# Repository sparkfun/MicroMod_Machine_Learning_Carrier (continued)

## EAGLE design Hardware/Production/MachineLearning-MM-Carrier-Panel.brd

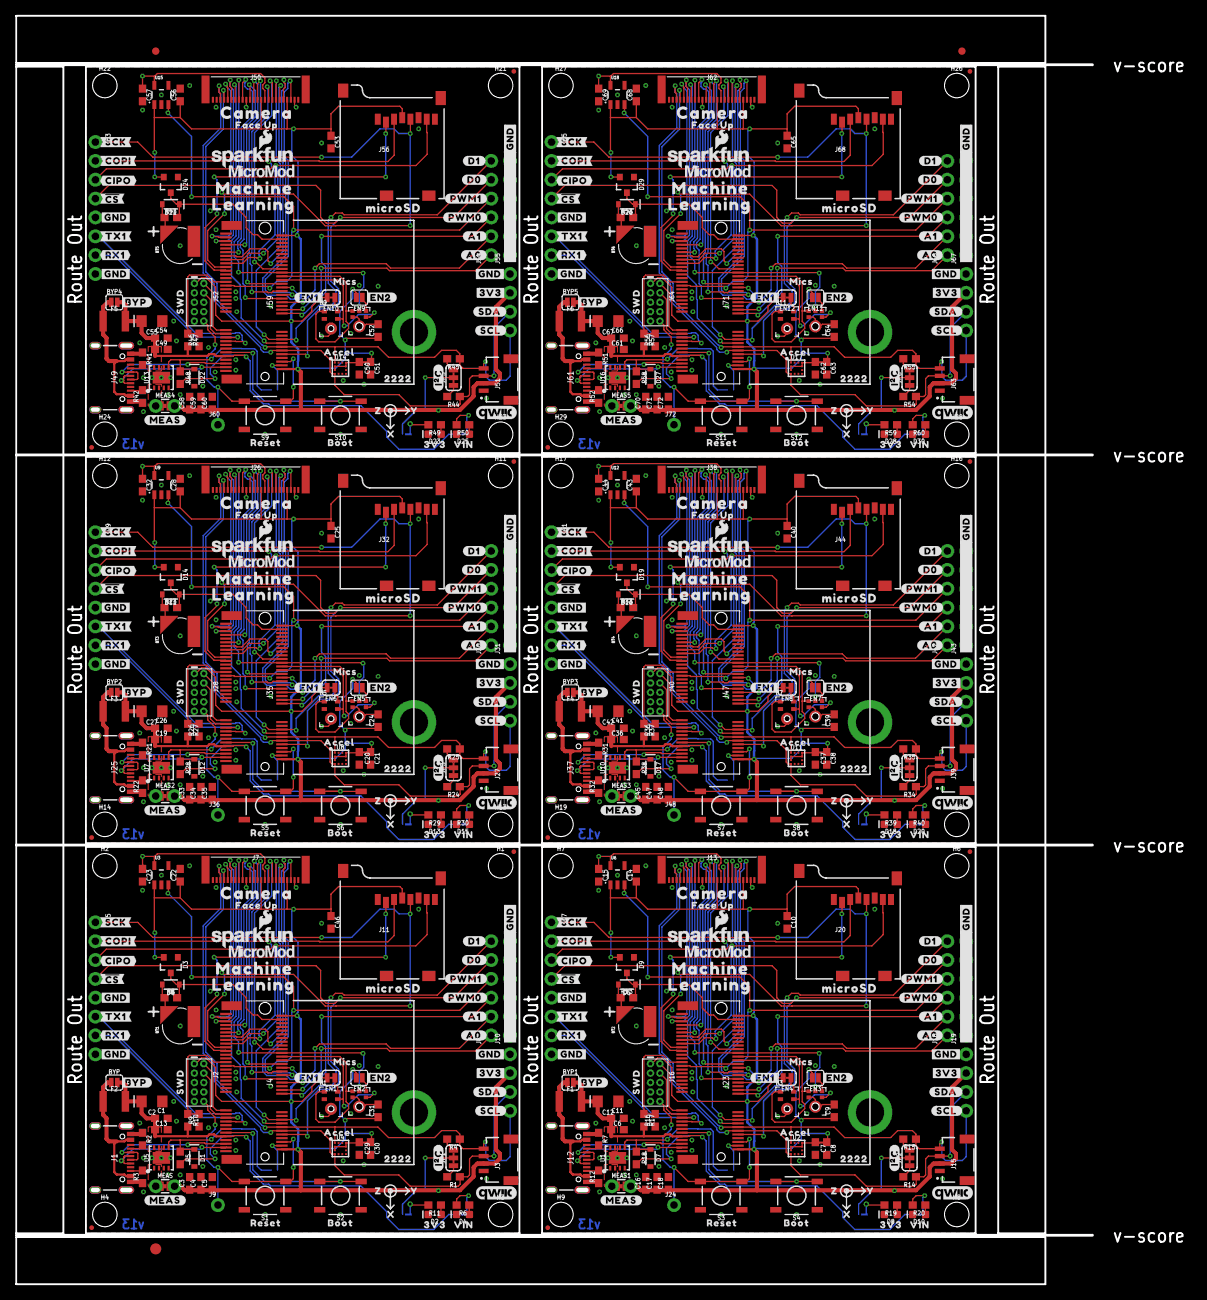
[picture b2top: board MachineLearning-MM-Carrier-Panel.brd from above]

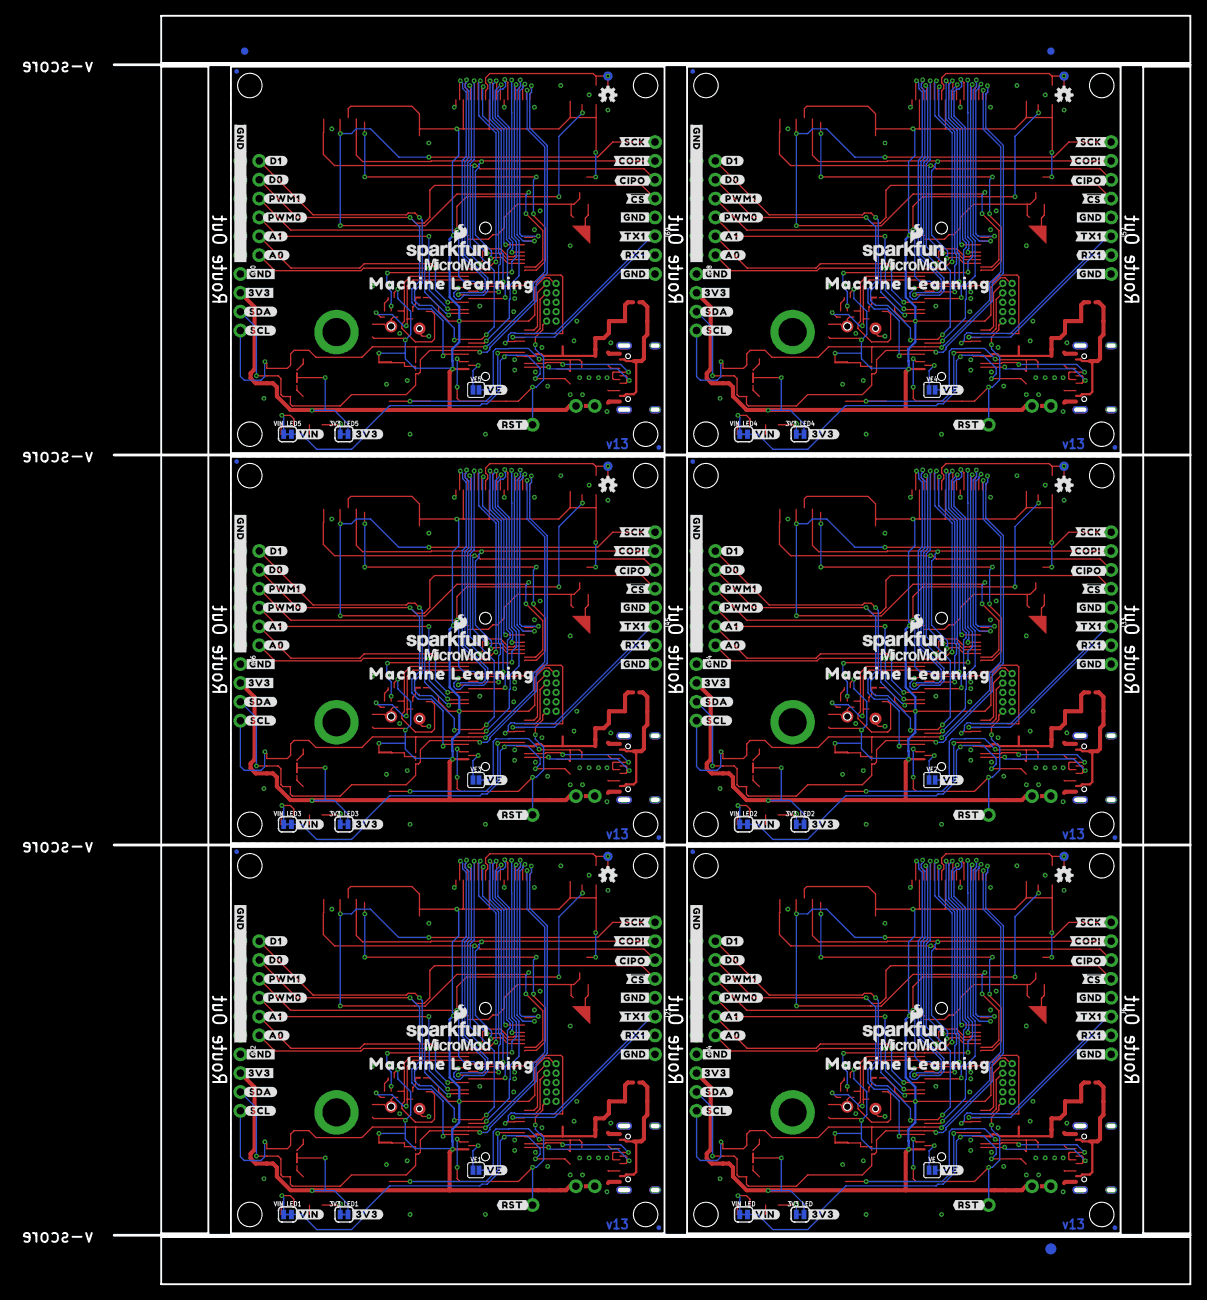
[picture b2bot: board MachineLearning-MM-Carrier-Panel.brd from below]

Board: 2 copper layers, 158.0 x 170.6 mm, 828 parts (219 on the bottom side), 336 nets.

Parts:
3V3_LED, 3V3_LED1, 3V3_LED2, 3V3_LED3, 3V3_LED4, 3V3_LED5: SMT-JUMPER_2_NC_TRACE_SILK
BT1, BT2, BT3, BT4, BT5, BT6: ML414H; ML414H_IV01E
BYP, BYP1, BYP2, BYP3, BYP4, BYP5: JUMPER-SMT_2_NO_SILK; SMT-JUMPER_2_NO_SILK
C1, C4, C8, C9, C10, C11, C15, C17, C21, C23, C24, C25, C26, C30, C31, C32, C34, C38, C39, C40, C41, C44, C46, C47, C51, C52, C53, C54, C57, C59, C63, C64, C65, C66, C69, C71: 0.1uF; 0603
C2, C12, C27, C42, C55, C67: 10uF; EIA3216
C3, C7, C14, C16, C20, C22, C28, C29, C33, C37, C43, C45, C50, C56, C58, C62, C68, C70: 1.0uF; 0603
C5, C6, C13, C18, C19, C35, C36, C48, C49, C60, C61, C72: 0.22uF; 0603
D1, D7, D12, D17, D22, D27: 3.3V; SOD-323
D2, D8, D13, D18, D23, D28: RED; LED-0603
D3, D9, D14, D19, D24, D29: BAS70-05; SOT23-3
D4, D10, D15, D20, D25, D30: Yellow; LED-0603
D5, D6, D11, D16, D21, D26: 3A/10V/280mV; SOD-323
E1, E3, E5, E7, E9, E11: SPH0641LM4H-1; SPH0641LM4H-1_MICROPHONE
E2, E4, E6, E8, E10, E12: ICS-43434
E$1, E$2, E$3, E$4: FIDUCIAL-1X2
E$5, E$6: FIDUCIAL-1.5X3
EN1, EN4, EN6, EN8, EN10, EN12: SMT-JUMPER_2_NC_TRACE_SILK
EN2, EN3, EN5, EN7, EN9, EN11: SMT-JUMPER_2_NO_SILK
F1, F2, F3, F4, F5, F6: 6V/2A; 1210
FD1, FD2, FD3, FD4, FD5, FD6, FD7, FD8, FD9, FD10, FD11, FD12, FD13, FD14, FD15, FD16, FD17, FD18, FD19, FD20, FD21, FD22, FD23, FD24: FIDUCIALUFIDUCIAL; FIDUCIAL-MICRO
H1, H2, H3, H4, H6, H7, H8, H9, H11, H12, H13, H14, H16, H17, H18, H19, H21, H22, H23, H24, H26, H27, H28, H29: STAND-OFF
H5, H10, H15, H20, H25, H30: STAND-OFF-REFLOW2.5MM_TALL; STAND-OFF-REFLOW-M2.5
J1, J12, J25, J37, J49, J61: USB-C-16P-2LAYER-PADS
J2, J16, J28, J40, J52, J64: JTAG; 2X5-PTH-1.27MM
J3, J15, J27, J39, J51, J63: QWIIC_RIGHT_ANGLE; JST04_1MM_RA
J4, J23, J35, J47, J59, J71: MICROMOD-2222-C; M.2-CONNECTOR-E
J5, J17, J29, J41, J53, J65: SPI; 1X05_NO_SILK
J6, J21, J33, J45, J57, J69: UART; 1X03_NO_SILK
J7, J13, J26, J38, J50, J62: CAMERA-HIMAXFACEUP; FPC05024-42201
J8, J18, J30, J42, J54, J66: Dedicated; 1X06_NO_SILK
J9, J24, J36, J48, J60, J72: 1X01_NO_SILK
J10, J19, J31, J43, J55, J67: 1X06_NO_SILK
J11, J20, J32, J44, J56, J68: microSD; MICRO-SD-SOCKET
J14, J22, J34, J46, J58, J70: 1X04_NO_SILK
JP1, JP2, JP3, JP4, JP5, JP6: SMT-JUMPER_3_2-NC_TRACE_SILK
LOGO1, LOGO4, LOGO5, LOGO8, LOGO9, LOGO12, LOGO13, LOGO16, LOGO17, LOGO20, LOGO21, LOGO24: SFE_LOGO_NAME_FLAME.1_INCH; SFE_LOGO_NAME_FLAME_.1
LOGO2, LOGO6, LOGO10, LOGO14, LOGO18, LOGO22: QWIIC_LOGO_CONNECTOR; QWIIC_5.5MM
LOGO3, LOGO7, LOGO11, LOGO15, LOGO19, LOGO23: OSHW-LOGOMINI; OSHW-LOGO-MINI
MEAS, MEAS1, MEAS2, MEAS3, MEAS4, MEAS5: COMBO-JUMPER_2_NC_TRACE
R1, R4, R14, R15, R24, R25, R34, R35, R44, R45, R54, R55: 2.2k; 0603
R2, R3, R7, R12, R21, R22, R31, R32, R41, R42, R51, R52: 5.1k; 0603
R5, R18, R28, R38, R48, R58: 100k; 0603
R6, R20, R30, R40, R50, R60: 4.7k; 0603
R8, R13, R23, R33, R43, R53: 3.3k; 0603
R9, R16, R26, R36, R46, R56: 10k; 0603
R10, R17, R27, R37, R47, R57: 20k; 0603
R11, R19, R29, R39, R49, R59: 1k; 0603
S1, S3, S5, S7, S9, S11: Reset; TACTILE_SWITCH_SMD_5.2MM
S2, S4, S6, S8, S10, S12: BOOT; TACTILE_SWITCH_SMD_5.2MM
TP1, TP2, TP3, TP4, TP5, TP7: TEST-POINT3X5; PAD.03X.05
U1, U5, U7, U10, U13, U16: AP7361C-33FGE; UDFN-8
U2, U4, U8, U11, U14, U17: LIS2DH12; LGA-12-LISDH12
U3, U6, U9, U12, U15, U18: AP2127K-1.8V; SOT23-5
U$1, U$117, U$184, U$251, U$318, U$385: #EN1#3
U$2, U$118, U$185, U$252, U$319, U$386: #EN2#4
U$3, U$128, U$195, U$262, U$329, U$396: CAMERA0
U$4, U$130, U$197, U$264, U$331, U$398: #3V3#0
U$5, U$122, U$189, U$256, U$323, U$390: MICS0
U$6, U$7, U$86, U$87, U$153, U$154, U$220, U$221, U$287, U$288, U$354, U$355: #A0#5
U$8, U$9, U$88, U$89, U$155, U$156, U$222, U$223, U$289, U$290, U$356, U$357: #A1#4
U$10, U$25, U$90, U$91, U$157, U$158, U$224, U$225, U$291, U$292, U$358, U$359: #D0#1
U$11, U$12, U$15, U$16, U$98, U$99, U$102, U$103, U$165, U$166, U$169, U$170, U$232, U$233, U$236, U$237, U$299, U$300, U$303, U$304, U$366, U$367, U$370, U$371: #GND#0
U$13, U$14, U$100, U$101, U$167, U$168, U$234, U$235, U$301, U$302, U$368, U$369: #3V3#1
U$17, U$123, U$190, U$257, U$324, U$391: #RST#1
U$18, U$124, U$191, U$258, U$325, U$392: #VE#0
U$19, U$119, U$186, U$253, U$320, U$387: #MEAS#2
U$20, U$131, U$198, U$265, U$332, U$399: #VIN#1
U$21, U$120, U$187, U$254, U$321, U$388: SWD0
U$22, U$129, U$196, U$263, U$330, U$397: FACE_UP0
U$23, U$125, U$192, U$259, U$326, U$393: #I�C#0
U$24, U$34, U$53, U$54, U$135, U$136, U$202, U$203, U$269, U$270, U$336, U$337: MICROMOD_LOGO_.35
U$26, U$37, U$126, U$134, U$193, U$201, U$260, U$268, U$327, U$335, U$394, U$402: MACHINE0
U$27, U$30, U$127, U$133, U$194, U$200, U$261, U$267, U$328, U$334, U$395, U$401: LEARNING1
U$28, U$132, U$199, U$266, U$333, U$400: MICROSD0
U$29, U$31, U$92, U$93, U$159, U$160, U$226, U$227, U$293, U$294, U$360, U$361: #D1#0
U$32, U$41, U$94, U$95, U$161, U$162, U$228, U$229, U$295, U$296, U$362, U$363: #PWM0#3
U$33, U$121, U$188, U$255, U$322, U$389: #BYP#1
U$35, U$55, U$56, U$68, U$137, U$138, U$204, U$205, U$271, U$272, U$338, U$339: ##CS##3
U$36, U$108, U$175, U$242, U$309, U$376: 3V37
U$38, U$109, U$176, U$243, U$310, U$377: 22223
U$39, U$110, U$177, U$244, U$311, U$378: ACCEL4
U$40, U$111, U$178, U$245, U$312, U$379: BOOT5
U$42, U$49, U$96, U$97, U$163, U$164, U$230, U$231, U$297, U$298, U$364, U$365: #PWM1#2
U$43, U$44, U$104, U$105, U$171, U$172, U$238, U$239, U$305, U$306, U$372, U$373: #SCL#3
U$45, U$112, U$179, U$246, U$313, U$380: RESET6
U$46, U$113, U$180, U$247, U$314, U$381: VIN8
U$47, U$114, U$181, U$248, U$315, U$382: X1
U$48, U$115, U$182, U$249, U$316, U$383: Y2
U$50, U$51, U$106, U$107, U$173, U$174, U$240, U$241, U$307, U$308, U$374, U$375: #SDA#2
U$52, U$116, U$183, U$250, U$317, U$384: Z0
U$57, U$58, U$69, U$70, U$139, U$140, U$206, U$207, U$273, U$274, U$340, U$341: #CIPO#2
U$59, U$60, U$71, U$72, U$141, U$142, U$208, U$209, U$275, U$276, U$342, U$343: #COPI#1
U$61, U$62, U$73, U$74, U$81, U$82, U$84, U$85, U$143, U$144, U$151, U$152, U$210, U$211, U$218, U$219, U$277, U$278, U$285, U$286, U$344, U$345, U$352, U$353: #GND#4
U$63, U$64, U$75, U$76, U$145, U$146, U$212, U$213, U$279, U$280, U$346, U$347: #RX1#6
U$65, U$66, U$77, U$78, U$147, U$148, U$214, U$215, U$281, U$282, U$348, U$349: #SCK#0
U$67, U$79, U$80, U$83, U$149, U$150, U$216, U$217, U$283, U$284, U$350, U$351: #TX1#5
VE, VE1, VE2, VE3, VE4, VE5: SMT-JUMPER_2_NO_SILK
VIN_LED, VIN_LED1, VIN_LED2, VIN_LED3, VIN_LED4, VIN_LED5: SMT-JUMPER_2_NC_TRACE_SILK

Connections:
1.8V: C23.1, J7.15, TP7.P$1, U3.5
1.8V1: C15.1, J13.15, TP1.P$1, U6.5
1.8V2: C32.1, J26.15, TP2.P$1, U9.5
1.8V3: C44.1, J38.15, TP3.P$1, U12.5
1.8V4: C57.1, J50.15, TP4.P$1, U15.5
1.8V5: C69.1, J62.15, TP5.P$1, U18.5
3.3V: 3V3_LED.2, C3.1, C4.1, C5.1, C22.1, C29.1, C30.1, C31.1, C46.1, D3.2, EN1.2, EN2.2, J2.1, J3.2, J4.2, J4.74, J7.14, J7.21, J11.VCC, J14.2, JP1.2, MEAS.2, MEAS.4, U3.1, U4.2, U4.3, U4.9, U4.10
3.3V1: 3V3_LED1.2, C7.1, C8.1, C9.1, C10.1, C14.1, C16.1, C17.1, C18.1, D9.2, EN3.2, EN4.2, J13.14, J13.21, J15.2, J16.1, J20.VCC, J22.2, J23.2, J23.74, JP2.2, MEAS1.2, MEAS1.4, U2.2, U2.3, U2.9, U2.10, U6.1
3.3V2: 3V3_LED2.2, C20.1, C21.1, C24.1, C25.1, C28.1, C33.1, C34.1, C35.1, D14.2, EN5.2, EN6.2, J26.14, J26.21, J27.2, J28.1, J32.VCC, J34.2, J35.2, J35.74, JP3.2, MEAS2.2, MEAS2.4, U8.2, U8.3, U8.9, U8.10, U9.1
3.3V3: 3V3_LED3.2, C37.1, C38.1, C39.1, C40.1, C43.1, C45.1, C47.1, C48.1, D19.2, EN7.2, EN8.2, J38.14, J38.21, J39.2, J40.1, J44.VCC, J46.2, J47.2, J47.74, JP4.2, MEAS3.2, MEAS3.4, U11.2, U11.3, U11.9, U11.10, U12.1
3.3V4: 3V3_LED4.2, C50.1, C51.1, C52.1, C53.1, C56.1, C58.1, C59.1, C60.1, D24.2, EN9.2, EN10.2, J50.14, J50.21, J51.2, J52.1, J56.VCC, J58.2, J59.2, J59.74, JP5.2, MEAS4.2, MEAS4.4, U14.2, U14.3, U14.9, U14.10, U15.1
3.3V5: 3V3_LED5.2, C62.1, C63.1, C64.1, C65.1, C68.1, C70.1, C71.1, C72.1, D29.2, EN11.2, EN12.2, J62.14, J62.21, J63.2, J64.1, J68.VCC, J70.2, J71.2, J71.74, JP6.2, MEAS5.2, MEAS5.4, U17.2, U17.3, U17.9, U17.10, U18.1
3.3V_EN: J4.4, VE.1
3.3V_EN1: J23.4, VE1.1
3.3V_EN2: J35.4, VE2.1
3.3V_EN3: J47.4, VE3.1
3.3V_EN4: J59.4, VE4.1
3.3V_EN5: J71.4, VE5.1
!BOOT!: J4.11, S2.3, S2.4
!BOOT!1: J23.11, S4.3, S4.4
!BOOT!2: J35.11, S6.3, S6.4
!BOOT!3: J47.11, S8.3, S8.4
!BOOT!4: J59.11, S10.3, S10.4
!BOOT!5: J71.11, S12.3, S12.4
!RESET!: J2.10, J4.6, J9.1, S1.3, S1.4
!RESET!1: J16.10, J23.6, J24.1, S3.3, S3.4
!RESET!2: J28.10, J35.6, J36.1, S5.3, S5.4
!RESET!3: J40.10, J47.6, J48.1, S7.3, S7.4
!RESET!4: J52.10, J59.6, J60.1, S9.3, S9.4
!RESET!5: J64.10, J71.6, J72.1, S11.3, S11.4
A0: J4.34, J8.1
A1: J4.38, J8.2
A2: J18.1, J23.34
A3: J18.2, J23.38
A4: J30.1, J35.34
A5: J30.2, J35.38
A6: J42.1, J47.34
A7: J42.2, J47.38
A8: J54.1, J59.34
A9: J54.2, J59.38
A10: J66.1, J71.34
A11: J66.2, J71.38
CAMERA_D0: J4.40, J7.11
CAMERA_D1: J4.42, J7.22
CAMERA_D2: J4.44, J7.16
CAMERA_D3: J4.46, J7.20
CAMERA_D4: J4.48, J7.13
CAMERA_D5: J4.73, J7.5
CAMERA_D6: J4.71, J7.6
CAMERA_D7: J4.69, J7.12
CAMERA_D8: J13.22, J23.42
CAMERA_D9: J13.20, J23.46
CAMERA_D10: J13.13, J23.48
CAMERA_D11: J13.5, J23.73
CAMERA_D12: J13.6, J23.71
CAMERA_D13: J13.12, J23.69
CAMERA_D14: J13.11, J23.40
CAMERA_D15: J13.16, J23.44
CAMERA_D16: J26.22, J35.42
CAMERA_D17: J26.20, J35.46
CAMERA_D18: J26.13, J35.48
CAMERA_D19: J26.5, J35.73
CAMERA_D20: J26.6, J35.71
CAMERA_D21: J26.12, J35.69
CAMERA_D22: J26.11, J35.40
CAMERA_D23: J26.16, J35.44
CAMERA_D24: J38.22, J47.42
CAMERA_D25: J38.20, J47.46
CAMERA_D26: J38.13, J47.48
CAMERA_D27: J38.5, J47.73
CAMERA_D28: J38.6, J47.71
CAMERA_D29: J38.12, J47.69
CAMERA_D30: J38.11, J47.40
CAMERA_D31: J38.16, J47.44
CAMERA_D32: J50.22, J59.42
CAMERA_D33: J50.20, J59.46
CAMERA_D34: J50.13, J59.48
CAMERA_D35: J50.5, J59.73
CAMERA_D36: J50.6, J59.71
CAMERA_D37: J50.12, J59.69
CAMERA_D38: J50.11, J59.40
CAMERA_D39: J50.16, J59.44
CAMERA_D40: J62.22, J71.42
CAMERA_D41: J62.20, J71.46
CAMERA_D42: J62.13, J71.48
CAMERA_D43: J62.5, J71.73
CAMERA_D44: J62.6, J71.71
CAMERA_D45: J62.12, J71.69
CAMERA_D46: J62.11, J71.40
CAMERA_D47: J62.16, J71.44
CAMERA_HSYNC: J4.65, J7.9
CAMERA_HSYNC1: J13.9, J23.65
CAMERA_HSYNC2: J26.9, J35.65
CAMERA_HSYNC3: J38.9, J47.65
CAMERA_HSYNC4: J50.9, J59.65
CAMERA_HSYNC5: J62.9, J71.65
CAMERA_INT: J4.16, J7.7
CAMERA_INT1: J13.7, J23.16
CAMERA_INT2: J26.7, J35.16
CAMERA_INT3: J38.7, J47.16
CAMERA_INT4: J50.7, J59.16
CAMERA_INT5: J62.7, J71.16
CAMERA_MCLK: J4.56, J7.17
CAMERA_MCLK1: J13.17, J23.56
CAMERA_MCLK2: J26.17, J35.56
CAMERA_MCLK3: J38.17, J47.56
CAMERA_MCLK4: J50.17, J59.56
CAMERA_MCLK5: J62.17, J71.56
CAMERA_VSYNC: J4.63, J7.19
CAMERA_VSYNC1: J13.19, J23.63
CAMERA_VSYNC2: J26.19, J35.63
CAMERA_VSYNC3: J38.19, J47.63
CAMERA_VSYNC4: J50.19, J59.63
CAMERA_VSYNC5: J62.19, J71.63
D0/HEADER_!CS!: J4.10, J5.4, J8.5
D0/HEADER_!CS!1: J17.4, J18.5, J23.10
D0/HEADER_!CS!2: J29.4, J30.5, J35.10
D0/HEADER_!CS!3: J41.4, J42.5, J47.10
D0/HEADER_!CS!4: J53.4, J54.5, J59.10
D0/HEADER_!CS!5: J65.4, J66.5, J71.10
D1/CAMERA_TRIG: J4.18, J7.18, J8.6
D1/CAMERA_TRIG1: J13.18, J18.6, J23.18
D1/CAMERA_TRIG2: J26.18, J30.6, J35.18
D1/CAMERA_TRIG3: J38.18, J42.6, J47.18
D1/CAMERA_TRIG4: J50.18, J54.6, J59.18
D1/CAMERA_TRIG5: J62.18, J66.6, J71.18
GND: BT1.-, C1.2, C2.-, C3.2, C4.2, C5.2, C13.2, C22.2, C23.2, C29.2, C30.2, C31.2, C46.2, D1.A, D2.C, D4.C, E1.2, E1.3, E1.6, E1.7, E1.8, E2.2, E2.3, E2.7, E2.8, E2.9, H5.1, J1.GND, J1.GND2, J2.3, J2.5, J2.9, J3.1, J4.1, J4.7, J4.33, J4.36, J4.39, J4.45, J4.75, J5.5, J6.3, J7.10, J7.23, J10.1, J10.2, J10.3, J10.4, J10.5, J10.6, J11.CD1, J11.GND, J11.GND1, J11.GND3, J14.1, R2.1, R3.1, R9.1, S1.1, S1.2, S2.1, S2.2, U3.2, U4.5, U4.6, U4.7, U4.8, U5.4, U5.EP
GND1: BT2.-, C6.2, C7.2, C8.2, C9.2, C10.2, C11.2, C12.-, C14.2, C15.2, C16.2, C17.2, C18.2, D7.A, D8.C, D10.C, E3.2, E3.3, E3.6, E3.7, E3.8, E4.2, E4.3, E4.7, E4.8, E4.9, H10.1, J12.GND, J12.GND2, J13.10, J13.23, J15.1, J16.3, J16.5, J16.9, J17.5, J19.1, J19.2, J19.3, J19.4, J19.5, J19.6, J20.CD1, J20.GND, J20.GND1, J20.GND3, J21.3, J22.1, J23.1, J23.7, J23.33, J23.36, J23.39, J23.45, J23.75, R7.1, R12.1, R16.1, S3.1, S3.2, S4.1, S4.2, U1.4, U1.EP, U2.5, U2.6, U2.7, U2.8, U6.2
GND2: BT3.-, C19.2, C20.2, C21.2, C24.2, C25.2, C26.2, C27.-, C28.2, C32.2, C33.2, C34.2, C35.2, D12.A, D13.C, D15.C, E5.2, E5.3, E5.6, E5.7, E5.8, E6.2, E6.3, E6.7, E6.8, E6.9, H15.1, J25.GND, J25.GND2, J26.10, J26.23, J27.1, J28.3, J28.5, J28.9, J29.5, J31.1, J31.2, J31.3, J31.4, J31.5, J31.6, J32.CD1, J32.GND, J32.GND1, J32.GND3, J33.3, J34.1, J35.1, J35.7, J35.33, J35.36, J35.39, J35.45, J35.75, R21.1, R22.1, R26.1, S5.1, S5.2, S6.1, S6.2, U7.4, U7.EP, U8.5, U8.6, U8.7, U8.8, U9.2
GND3: BT4.-, C36.2, C37.2, C38.2, C39.2, C40.2, C41.2, C42.-, C43.2, C44.2, C45.2, C47.2, C48.2, D17.A, D18.C, D20.C, E7.2, E7.3, E7.6, E7.7, E7.8, E8.2, E8.3, E8.7, E8.8, E8.9, H20.1, J37.GND, J37.GND2, J38.10, J38.23, J39.1, J40.3, J40.5, J40.9, J41.5, J43.1, J43.2, J43.3, J43.4, J43.5, J43.6, J44.CD1, J44.GND, J44.GND1, J44.GND3, J45.3, J46.1, J47.1, J47.7, J47.33, J47.36, J47.39, J47.45, J47.75, R31.1, R32.1, R36.1, S7.1, S7.2, S8.1, S8.2, U10.4, U10.EP, U11.5, U11.6, U11.7, U11.8, U12.2
GND4: BT5.-, C49.2, C50.2, C51.2, C52.2, C53.2, C54.2, C55.-, C56.2, C57.2, C58.2, C59.2, C60.2, D22.A, D23.C, D25.C, E9.2, E9.3, E9.6, E9.7, E9.8, E10.2, E10.3, E10.7, E10.8, E10.9, H25.1, J49.GND, J49.GND2, J50.10, J50.23, J51.1, J52.3, J52.5, J52.9, J53.5, J55.1, J55.2, J55.3, J55.4, J55.5, J55.6, J56.CD1, J56.GND, J56.GND1, J56.GND3, J57.3, J58.1, J59.1, J59.7, J59.33, J59.36, J59.39, J59.45, J59.75, R41.1, R42.1, R46.1, S9.1, S9.2, S10.1, S10.2, U13.4, U13.EP, U14.5, U14.6, U14.7, U14.8, U15.2
GND5: BT6.-, C61.2, C62.2, C63.2, C64.2, C65.2, C66.2, C67.-, C68.2, C69.2, C70.2, C71.2, C72.2, D27.A, D28.C, D30.C, E11.2, E11.3, E11.6, E11.7, E11.8, E12.2, E12.3, E12.7, E12.8, E12.9, H30.1, J61.GND, J61.GND2, J62.10, J62.23, J63.1, J64.3, J64.5, J64.9, J65.5, J67.1, J67.2, J67.3, J67.4, J67.5, J67.6, J68.CD1, J68.GND, J68.GND1, J68.GND3, J69.3, J70.1, J71.1, J71.7, J71.33, J71.36, J71.39, J71.45, J71.75, R51.1, R52.1, R56.1, S11.1, S11.2, S12.1, S12.2, U16.4, U16.EP, U17.5, U17.6, U17.7, U17.8, U18.2
I2C_SCL: J3.4, J4.14, J7.4, J14.4, R4.1, U4.1
I2C_SCL1: J13.4, J15.4, J22.4, J23.14, R15.1, U2.1
I2C_SCL2: J26.4, J27.4, J34.4, J35.14, R25.1, U8.1
I2C_SCL3: J38.4, J39.4, J46.4, J47.14, R35.1, U11.1
I2C_SCL4: J50.4, J51.4, J58.4, J59.14, R45.1, U14.1
I2C_SCL5: J62.4, J63.4, J70.4, J71.14, R55.1, U17.1
I2C_SDA: J3.3, J4.12, J7.3, J14.3, R1.1, U4.4
I2C_SDA1: J13.3, J15.3, J22.3, J23.12, R14.1, U2.4
I2C_SDA2: J26.3, J27.3, J34.3, J35.12, R24.1, U8.4
I2C_SDA3: J38.3, J39.3, J46.3, J47.12, R34.1, U11.4
I2C_SDA4: J50.3, J51.3, J58.3, J59.12, R44.1, U14.4
I2C_SDA5: J62.3, J63.3, J70.3, J71.12, R54.1, U17.4
I2S_SCK/PDM_CLK: E1.4, E2.4, J4.50
I2S_SCK/PDM_CLK1: E3.4, E4.4, J23.50
I2S_SCK/PDM_CLK2: E5.4, E6.4, J35.50
I2S_SCK/PDM_CLK3: E7.4, E8.4, J47.50
I2S_SCK/PDM_CLK4: E9.4, E10.4, J59.50
I2S_SCK/PDM_CLK5: E11.4, E12.4, J71.50
I2S_SD/CAMERA_PCLK: E2.6, J4.54, J7.8
I2S_SD/CAMERA_PCLK1: E4.6, J13.8, J23.54
I2S_SD/CAMERA_PCLK2: E6.6, J26.8, J35.54
I2S_SD/CAMERA_PCLK3: E8.6, J38.8, J47.54
I2S_SD/CAMERA_PCLK4: E10.6, J50.8, J59.54
I2S_SD/CAMERA_PCLK5: E12.6, J62.8, J71.54
I2S_WS/PDM_DAT: E1.1, E2.1, J4.52
I2S_WS/PDM_DAT1: E3.1, E4.1, J23.52
I2S_WS/PDM_DAT2: E5.1, E6.1, J35.52
I2S_WS/PDM_DAT3: E7.1, E8.1, J47.52
I2S_WS/PDM_DAT4: E9.1, E10.1, J59.52
I2S_WS/PDM_DAT5: E11.1, E12.1, J71.52
unnamed: R6.2, VIN_LED.1
unnamed: JP1.3, R4.2
unnamed: JP1.1, R1.2
unnamed: E1.5, EN1.1
unnamed: E2.5, EN2.1
unnamed: 3V3_LED.1, R11.2
unnamed: D2.A, R11.1
unnamed: D4.A, R6.1
unnamed: J12.A5, R7.2
unnamed: J1.A5, R2.2
unnamed: J1.B5, R3.2
unnamed: D1.C, R5.1, U5.5, VE.2
unnamed: J12.B5, R12.2
unnamed: BT1.+, D6.A, R8.1
unnamed: BT2.+, D5.A, R13.1
unnamed: JP2.3, R15.2
unnamed: JP2.1, R14.2
unnamed: E3.5, EN4.1
unnamed: E4.5, EN3.1
unnamed: 3V3_LED1.1, R19.2
unnamed: D8.A, R19.1
unnamed: R20.2, VIN_LED1.1
unnamed: D10.A, R20.1
unnamed: D7.C, R18.1, U1.5, VE1.2
unnamed: J25.A5, R21.2
unnamed: J25.B5, R22.2
unnamed: BT3.+, D11.A, R23.1
unnamed: JP3.3, R25.2
unnamed: JP3.1, R24.2
unnamed: E5.5, EN6.1
unnamed: E6.5, EN5.1
unnamed: 3V3_LED2.1, R29.2
unnamed: D13.A, R29.1
unnamed: R30.2, VIN_LED2.1
unnamed: D15.A, R30.1
unnamed: D12.C, R28.1, U7.5, VE2.2
unnamed: J37.A5, R31.2
unnamed: J37.B5, R32.2
unnamed: BT4.+, D16.A, R33.1
unnamed: JP4.3, R35.2
unnamed: JP4.1, R34.2
unnamed: E7.5, EN8.1
unnamed: E8.5, EN7.1
unnamed: 3V3_LED3.1, R39.2
unnamed: D18.A, R39.1
unnamed: R40.2, VIN_LED3.1
unnamed: D20.A, R40.1
unnamed: D17.C, R38.1, U10.5, VE3.2
unnamed: J49.A5, R41.2
unnamed: J49.B5, R42.2
unnamed: BT5.+, D21.A, R43.1
unnamed: JP5.3, R45.2
unnamed: JP5.1, R44.2
unnamed: E9.5, EN10.1
unnamed: E10.5, EN9.1
unnamed: 3V3_LED4.1, R49.2
unnamed: D23.A, R49.1
unnamed: R50.2, VIN_LED4.1
unnamed: D25.A, R50.1
unnamed: D22.C, R48.1, U13.5, VE4.2
unnamed: J61.A5, R51.2
unnamed: J61.B5, R52.2
unnamed: BT6.+, D26.A, R53.1
unnamed: JP6.3, R55.2
unnamed: JP6.1, R54.2
unnamed: E11.5, EN12.1
unnamed: E12.5, EN11.1
unnamed: 3V3_LED5.1, R59.2
unnamed: D28.A, R59.1
unnamed: R60.2, VIN_LED5.1
unnamed: D30.A, R60.1
unnamed: D27.C, R58.1, U16.5, VE5.2
PWM0: J4.32, J8.3
PWM1: J18.3, J23.32
PWM1/CAM_VDD: J4.47, J8.4, U3.3
PWM1/CAM_VDD1: J18.4, J23.47, U6.3
PWM1/CAM_VDD2: J30.4, J35.47, U9.3
PWM1/CAM_VDD3: J42.4, J47.47, U12.3
PWM1/CAM_VDD4: J54.4, J59.47, U15.3
PWM1/CAM_VDD5: J66.4, J71.47, U18.3
PWM2: J30.3, J35.32
PWM3: J42.3, J47.32
PWM4: J54.3, J59.32
PWM5: J66.3, J71.32
RTC_3V: D3.3, D6.C, J4.72, R8.2
RTC_3V1: D5.C, D9.3, J23.72, R13.2
RTC_3V2: D11.C, D14.3, J35.72, R23.2
RTC_3V3: D16.C, D19.3, J47.72, R33.2
RTC_3V4: D21.C, D24.3, J59.72, R43.2
RTC_3V5: D26.C, D29.3, J71.72, R53.2
RX1: J4.19, J6.2
RX2: J21.2, J23.19
RX3: J33.2, J35.19
RX4: J45.2, J47.19
RX5: J57.2, J59.19
RX6: J69.2, J71.19
SPI_!CS!: J4.55, J11.CS/DAT3
SPI_!CS!1: J20.CS/DAT3, J23.55
SPI_!CS!2: J32.CS/DAT3, J35.55
SPI_!CS!3: J44.CS/DAT3, J47.55
SPI_!CS!4: J56.CS/DAT3, J59.55
SPI_!CS!5: J68.CS/DAT3, J71.55
SPI_CIPO: J4.61, J5.3, J11.DO/DAT0
SPI_CIPO1: J17.3, J20.DO/DAT0, J23.61
SPI_CIPO2: J29.3, J32.DO/DAT0, J35.61
SPI_CIPO3: J41.3, J44.DO/DAT0, J47.61
SPI_CIPO4: J53.3, J56.DO/DAT0, J59.61
SPI_CIPO5: J65.3, J68.DO/DAT0, J71.61
SPI_COPI: J4.59, J5.2, J11.DI/CMD
SPI_COPI1: J17.2, J20.DI/CMD, J23.59
SPI_COPI2: J29.2, J32.DI/CMD, J35.59
SPI_COPI3: J41.2, J44.DI/CMD, J47.59
SPI_COPI4: J53.2, J56.DI/CMD, J59.59
SPI_COPI5: J65.2, J68.DI/CMD, J71.59
SPI_SCK: J4.57, J5.1, J11.SCLK
SPI_SCK1: J17.1, J20.SCLK, J23.57
SPI_SCK2: J29.1, J32.SCLK, J35.57
SPI_SCK3: J41.1, J44.SCLK, J47.57
SPI_SCK4: J53.1, J56.SCLK, J59.57
SPI_SCK5: J65.1, J68.SCLK, J71.57
SWDCK: J2.4, J4.21
SWDCK1: J16.4, J23.21
SWDCK2: J28.4, J35.21
SWDCK3: J40.4, J47.21
SWDCK4: J52.4, J59.21
SWDCK5: J64.4, J71.21
SWDIO: J2.2, J4.23
SWDIO1: J16.2, J23.23
SWDIO2: J28.2, J35.23
SWDIO3: J40.2, J47.23
SWDIO4: J52.2, J59.23
SWDIO5: J64.2, J71.23
TX1: J4.17, J6.1
TX2: J21.1, J23.17
TX3: J33.1, J35.17
TX4: J45.1, J47.17
TX5: J57.1, J59.17
TX6: J69.1, J71.17
USB_D+: J1.A6, J1.B6, J4.3
USB_D+1: J12.A6, J12.B6, J23.3
USB_D+2: J25.A6, J25.B6, J35.3
USB_D+3: J37.A6, J37.B6, J47.3
USB_D+4: J49.A6, J49.B6, J59.3
USB_D+5: J61.A6, J61.B6, J71.3
USB_D-: J1.A7, J1.B7, J4.5
USB_D-1: J12.A7, J12.B7, J23.5
USB_D-2: J25.A7, J25.B7, J35.5
USB_D-3: J37.A7, J37.B7, J47.5
USB_D-4: J49.A7, J49.B7, J59.5
USB_D-5: J61.A7, J61.B7, J71.5
VIN: BYP.2, C1.1, C2.+, C13.1, F2.2, J4.9, R5.2, R10.2, U5.8, VIN_LED.2
VIN1: BYP1.2, C6.1, C11.1, C12.+, F1.2, J23.9, R17.2, R18.2, U1.8, VIN_LED1.2
VIN2: BYP2.2, C19.1, C26.1, C27.+, F3.2, J35.9, R27.2, R28.2, U7.8, VIN_LED2.2
VIN3: BYP3.2, C36.1, C41.1, C42.+, F4.2, J47.9, R37.2, R38.2, U10.8, VIN_LED3.2
VIN4: BYP4.2, C49.1, C54.1, C55.+, F5.2, J59.9, R47.2, R48.2, U13.8, VIN_LED4.2
VIN5: BYP5.2, C61.1, C66.1, C67.+, F6.2, J71.9, R57.2, R58.2, U16.8, VIN_LED5.2
VIN/1: J23.49, R16.2, R17.1
VIN/2: J35.49, R26.2, R27.1
VIN/3: J4.49, R9.2, R10.1
VIN/4: J47.49, R36.2, R37.1
VIN/5: J59.49, R46.2, R47.1
VIN/6: J71.49, R56.2, R57.1
VREG_3.3V: MEAS.1, MEAS.3, U5.1
VREG_3.3V1: MEAS1.1, MEAS1.3, U1.1
VREG_3.3V2: MEAS2.1, MEAS2.3, U7.1
VREG_3.3V3: MEAS3.1, MEAS3.3, U10.1
VREG_3.3V4: MEAS4.1, MEAS4.3, U13.1
VREG_3.3V5: MEAS5.1, MEAS5.3, U16.1
V_USB: BYP.1, F2.1, J1.VBUS1, J1.VBUS2
V_USB1: BYP1.1, F1.1, J12.VBUS1, J12.VBUS2
V_USB2: BYP2.1, F3.1, J25.VBUS1, J25.VBUS2
V_USB3: BYP3.1, F4.1, J37.VBUS1, J37.VBUS2
V_USB4: BYP4.1, F5.1, J49.VBUS1, J49.VBUS2
V_USB5: BYP5.1, F6.1, J61.VBUS1, J61.VBUS2

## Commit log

2020-04-07 Update MM connector. Remove backup files. Add ignore.
2020-04-23 v11 routed
2020-04-27 Change RTC charge to 3.3k. Add bulk cap to vreg output.
2020-05-04 Update micromod connector to new SPI pinout
2020-05-04 Fix route to SPI SCK
2020-05-05 Update v-reg device
2020-08-14 Re-route camera connector for face up. Convert buzzard labels. Add power control to camera regulator.
2020-08-14 Remove old test file
2020-09-10 Update MicroMod connector with SPI port changes
2020-09-10 Rename SPI lines for clarification
2020-09-10 Update production files to v13
2020-11-20 Create License.md
    Added license
2022-05-27 Update schematic with correct 0x24 camera I2C address
